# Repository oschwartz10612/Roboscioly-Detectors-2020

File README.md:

# Roboscioly-Detectors-2020

This project is designed to take the temperature of an unknown cup of water via reading the ADC output of a thermistor

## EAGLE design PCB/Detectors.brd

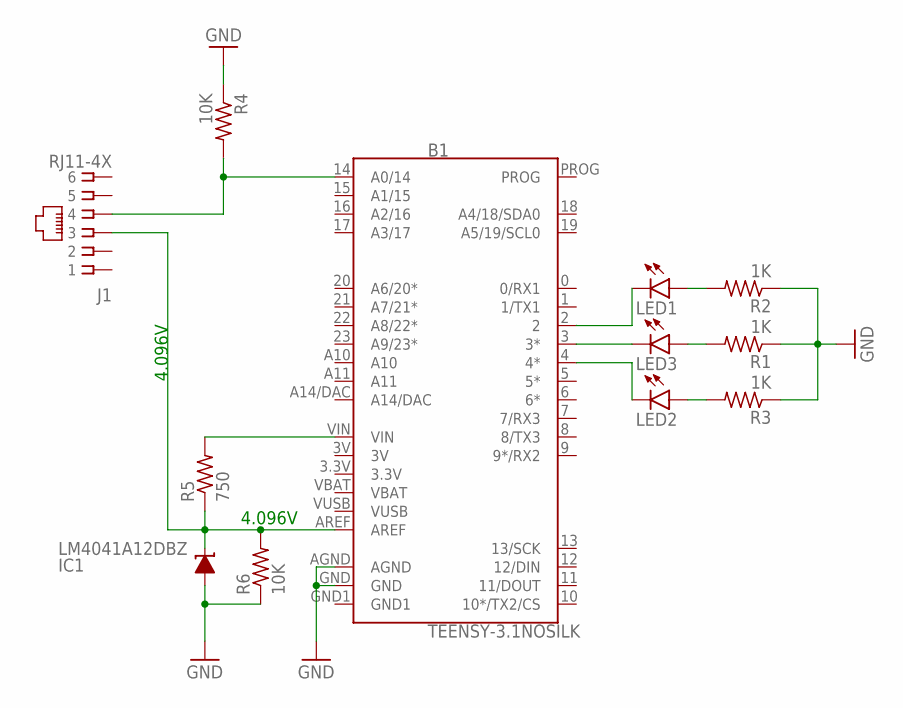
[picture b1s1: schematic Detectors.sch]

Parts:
B1: TEENSY-3.1NOSILK; TEENSY-3.1_NOSILK
IC1: LM4041A12DBZ; DBZ_R-PDSO-G3
J1: RJ11-4X; RJ11-NO_SHIELD
LED1, LED2, LED3: LED5MM
R1, R2, R3: 1K; R0805
R4, R6: 10K; R0805
R5: 750; R0805

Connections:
3.3V: B1.3.3V
3V: B1.3V
GND: B1.AGND, B1.GND, IC1.2 (A), R1.1, R2.1, R3.1, R4.1, R6.1
GND1: B1.GND1
unnamed: B1.AREF, IC1.1 (C), J1.3, R5.1, R6.2
unnamed: LED2.A, R3.2
unnamed: LED3.A, R1.2
unnamed: LED1.A, R2.2
unnamed: B1.2, LED1.K (C)
unnamed: B1.3 (3*), LED3.K (C)
unnamed: B1.4 (4*), LED2.K (C)
unnamed: B1.VIN, R5.2
unnamed: B1.14 (A0/14), J1.4, R4.2
VBAT: B1.VBAT
VUSB: B1.VUSB

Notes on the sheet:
4.096V

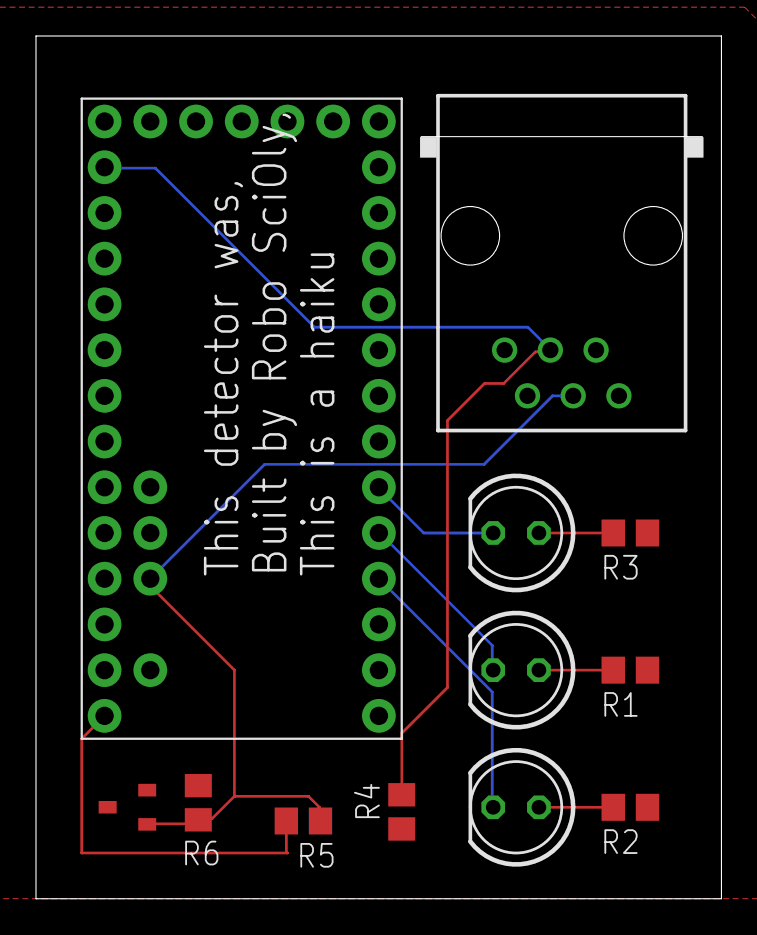
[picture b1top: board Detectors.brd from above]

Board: 2 copper layers, 38.1 x 47.9 mm, 12 parts (0 on the bottom side), 10 nets.

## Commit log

2019-11-14 added PCB files
2019-11-14 added gitignore
2019-11-18 setup enviroment
2019-11-18 remomved travis
2019-11-28 first code interation
2019-12-05 added LEDs
2019-12-05 adc library
2019-12-05 checkpoint
2019-12-06 changed b value
2019-12-06 small valued
2019-12-06 fixed beta value
2019-12-06 changed stinehart math
2019-12-06 stefan
2019-12-07 last resort
2019-12-07 DONE
2019-12-07 uncommented leds
2019-12-12 made fairfax branch & fixed LEDs
2019-12-19 testing with arduino
2019-12-23 new PCB
2019-12-23 stuff and things
2019-12-23 Stefan saves several sections successfully
2019-12-23 it works
2019-12-23 Final files find friendship file formats of fgithub
2019-12-23 data collection branch
2019-12-23 changed critical values
2019-12-23 changed crutial values and added reference
2019-12-23 updated PCB and scematic
2019-12-23 for merge
2020-01-11 final Fairfax code
2020-02-03 Adjusted valused and addded =
2020-02-03 Adjusted timing and voltage
2020-02-03 Added new function and adjusted for breadboard
    Added test data function
    Commented refrence code
    Changed to 3.3v voltage source
2020-02-05 Added Feb 3rd Test Data
    Changed to 3.3v & breadboard
2020-02-12 Function added for Regionals
2020-02-14 Wibbly wobbily woo, I wrote some code for you!

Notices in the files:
parts and their libraries:
SparkFun-Boards: Licensing: Creative Commons ShareAlike 4.0 International - https://creativecommons.org/licenses/by-sa/4.0
